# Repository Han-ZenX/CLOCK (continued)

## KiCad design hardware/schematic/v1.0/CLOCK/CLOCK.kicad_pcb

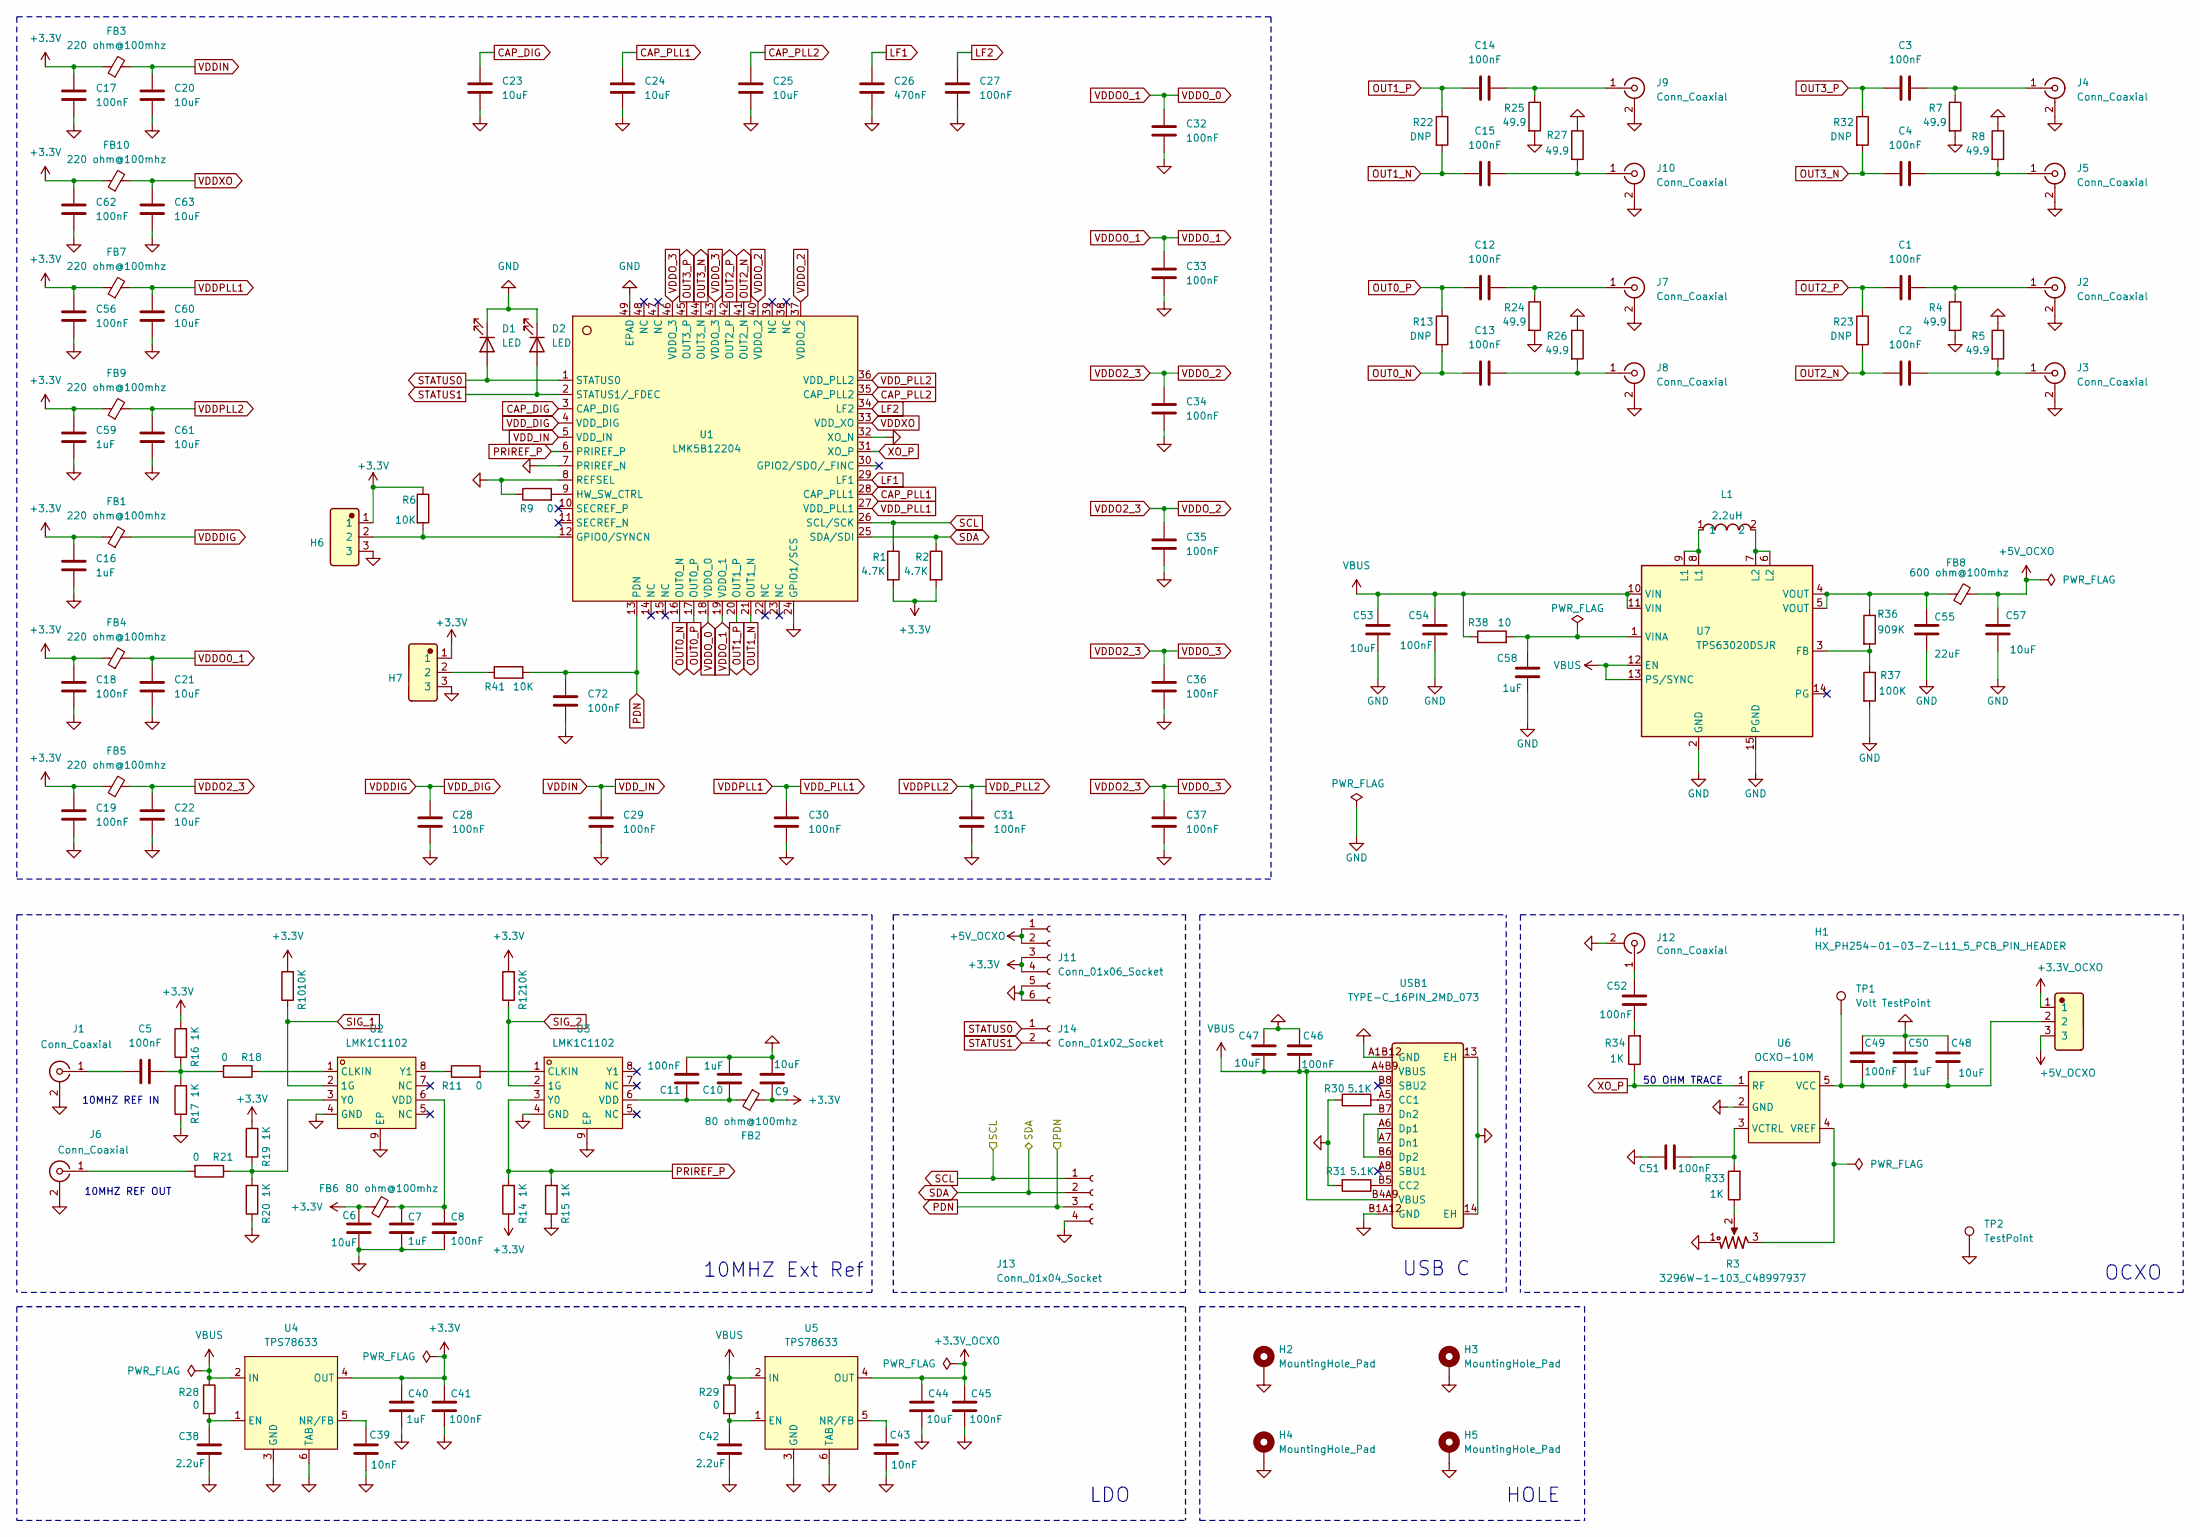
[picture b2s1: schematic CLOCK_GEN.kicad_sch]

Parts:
C1, C2, C3, C4, C5, C8, C11, C12, C13, C14, C15, C17, C18, C19, C27, C28, C29, C30, C31, C32, C33, C34, C35, C36, C37, C41, C45, C46, C49, C51, C52, C54, C56, C62, C72: 100nF; C_0402_1005Metric
C6, C9, C20, C21, C22, C23, C24, C25, C47, C60, C61, C63: 10uF; C_0402_1005Metric
C7, C10, C16, C40, C50, C59: 1uF; C_0402_1005Metric
C26: 470nF; C_0402_1005Metric
C38, C42: 2.2uF; C_0603_1608Metric
C39, C43: 10nF; C_0402_1005Metric
C44: 10uF; C_0805_2012Metric
C48, C53, C57: 10uF; C_0603_1608Metric
C55: 22uF; C_0805_2012Metric
C58: 1uF; C_0603_1608Metric
D1, D2: LED; LED_0603_1608Metric
FB1, FB3, FB4, FB5, FB7, FB9, FB10: 220 ohm@100mhz; L_0603_1608Metric
FB2, FB6: 80 ohm@100mhz; L_0603_1608Metric
FB8: 600 ohm@100mhz; L_0603_1608Metric
H1, H6, H7: HX_PH254-01-03-Z-L11_5_PCB_PIN_HEADER; Manufacturer Part HX PH254-01-03-Z-L11.5 pcb pin header; LCSC C52016391
H2, H3, H4, H5: MountingHole_Pad; MountingHole_3.2mm_M3_Pad
J1, J2, J3, J4, J5, J6, J7, J8, J9, J10, J12: Conn_Coaxial; SMA_Amphenol_132289_EdgeMount
J11: Conn_01x06_Socket; PinSocket_1x06_P2.54mm_Vertical
J13: Conn_01x04_Socket; PinHeader_1x04_P2.54mm_Vertical
J14: Conn_01x02_Socket; PinSocket_1x02_P2.54mm_Vertical
L1: 2.2uH; FNR4030S2R2MT; Manufacturer Part FNR4030S2R2MT; LCSC C167869
R1, R2: 4.7K; R_0603_1608Metric
R3: 3296W-1-103_C48997937; Manufacturer Part 3296W-1-103; LCSC C48997937
R4, R5, R7, R8, R24, R25, R26, R27: 49.9; R_0402_1005Metric
R6: 10K; R_0603_1608Metric
R9, R11, R18, R21, R28, R29: 0; R_0402_1005Metric
R10, R12, R41: 10K; R_0402_1005Metric
R13, R22, R23, R32: DNP; R_0402_1005Metric
R14, R15, R16, R17, R19, R20, R33, R34: 1K; R_0402_1005Metric
R30, R31: 5.1K; R_0402_1005Metric
R36: 909K; R_0603_1608Metric
R37: 100K; R_0603_1608Metric
R38: 10; R_0402_1005Metric
TP1: Volt TestPoint; TestPoint_Pad_D1.0mm
TP2: TestPoint; TestPoint_Loop_D1.80mm_Drill1.0mm_Beaded
U1: LMK5B12204; VQFN-48-1EP_7x7mm_P0.5mm_EP5.15x5.15mm_ThermalVias
U2, U3: LMK1C1102; WSON-8-1EP_2x2mm_P0.5mm_EP0.9x1.6mm
U4, U5: TPS78633; TPS78633DCQR
U6: OCXO-10M; DOPFITKR2-10M
U7: TPS63020DSJR
USB1: TYPE-C_16PIN_2MD_073; Manufacturer Part TYPE-C 16PIN 2MD(073); LCSC C2765186

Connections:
+3.3V: C6.2, C9.2, C16.2, C17.2, C18.2, C19.2, C40.1, C41.1, C56.2, C59.2, C62.2, FB1.1, FB2.1, FB3.1, FB4.1, FB5.1, FB6.1, FB7.1, FB9.1, FB10.1, H6.1, H7.1, J11.3, J11.4, R1.2, R2.2, R6.1, R10.2, R12.2, R14.1, R16.2, R19.2, U4.4 (OUT); also elsewhere on the board
+3.3V_OCXO: C44.1, C45.1, H1.1, U5.4 (OUT)
+5V_OCXO: C57.1, FB8.2, H1.3, J11.1, J11.2
CAP_DIG: C23.2, U1.3 (CAP_DIG)
CAP_PLL1: C24.2, U1.28 (CAP_PLL1)
CAP_PLL2: C25.2, U1.35 (CAP_PLL2)
GND: C6.1, C7.1, C8.1, C9.1, C10.1, C11.1, C16.1, C17.1, C18.1, C19.1, C20.1, C21.1, C22.1, C23.1, C24.1, C25.1, C26.1, C27.1, C28.1, C29.1, C30.1, C31.1, C32.1, C33.1, C34.1, C35.1, C36.1, C37.1, C38.1, C39.2, C40.2, C41.2, C42.1, C43.2, C44.2, C45.2, C46.2, C47.1, C48.1, C49.2, C50.1, C51.2, C53.2, C54.2, C55.2, C56.1, C57.2, C58.2, C59.1, C60.1, C61.1, C62.1, C63.1, C72.1, D1.1 (K), D2.1 (K), H2.1 (1_1), H3.1 (1_1), H4.1 (1_1), H5.1 (1_1), H6.3, H7.3, J1.2 (Ext), J2.2 (Ext), J3.2 (Ext), J4.2 (Ext), J5.2 (Ext), J6.2 (Ext), J7.2 (Ext), J8.2 (Ext), J9.2 (Ext), J10.2 (Ext), J11.5, J11.6, J12.2 (Ext), J13.4, R3.1, R4.2, R5.1, R7.2, R8.1, R9.1, R15.1, R17.1, R20.1, R24.2, R25.2, R26.1, R27.1, R30.1, R31.2, R37.2, TP2.1 (1_1), U1.7 (PRIREF_N), U1.8 (REFSEL), U1.24 (GPIO1/SCS), U1.32 (XO_N), U1.49 (EPAD), U2.4 (GND), U2.9 (EP), U3.4 (GND), U3.9 (EP), U4.3 (GND), U4.6 (TAB), U5.3 (GND), U5.6 (TAB), U6.2 (GND), U7.2 (GND), U7.15 (PGND), USB1.13 (EH), USB1.14 (EH), USB1.A1B12 (GND), USB1.B1A12 (GND); also elsewhere on the board
LF1: C26.2, U1.29 (LF1)
LF2: C27.2, U1.34 (LF2)
unnamed: C5.2, R16.1, R17.2, R18.2
unnamed: C52.2, R34.2
unnamed: C55.1, FB8.1, R36.1, U7.4 (VOUT), U7.5 (VOUT)
unnamed: H7.2, R41.1
unnamed: C5.1, J1.1 (In)
unnamed: C1.2, J2.1 (In), R4.1
unnamed: C2.2, J3.1 (In), R5.2
unnamed: C3.2, J4.1 (In), R7.1
unnamed: C4.1, J5.1 (In), R8.2
unnamed: J6.1 (In), R21.2
unnamed: C12.2, J7.1 (In), R24.1
unnamed: C13.2, J8.1 (In), R26.2
unnamed: C14.2, J9.1 (In), R25.1
unnamed: C15.1, J10.1 (In), R27.2
unnamed: C52.1, J12.1 (In)
unnamed: L1.1, U7.8 (L1), U7.9 (L1)
unnamed: L1.2, U7.6 (L2), U7.7 (L2)
unnamed: R3.2, R33.1
unnamed: H6.2, R6.2, U1.12 (GPIO0/SYNCN)
unnamed: R9.2, U1.9 (HW_SW_CTRL)
unnamed: R18.1, U2.1 (CLKIN)
unnamed: C7.2, C8.2, FB6.2, U2.6 (VDD)
unnamed: R19.1, R20.2, R21.1, U2.3 (Y0)
unnamed: R11.1, U2.8 (Y1)
unnamed: R11.2, U3.1 (CLKIN)
unnamed: C10.2, C11.2, FB2.2, U3.6 (VDD)
unnamed: C38.2, R28.2, U4.1 (EN)
unnamed: C39.1, U4.5 (NR/FB)
unnamed: C42.2, R29.2, U5.1 (EN)
unnamed: C43.1, U5.5 (NR/FB)
unnamed: C48.2, C49.1, C50.2, H1.2, TP1.1 (1_1), U6.5 (VCC)
unnamed: C51.1, R33.2, U6.3 (VCTRL)
unnamed: R3.3, U6.4 (VREF)
unnamed: R36.2, R37.1, U7.3 (FB)
unnamed: C58.1, R38.2, U7.1 (VINA)
unnamed: R30.2, USB1.A5 (CC1)
unnamed: R31.1, USB1.B5 (CC2)
unnamed: USB1.A6 (Dp1), USB1.A7 (Dn1)
unnamed: USB1.B6 (Dp2), USB1.B7 (Dn2)
OUT0_N: C13.1, R13.2, U1.16 (OUT0_N)
OUT0_P: C12.1, R13.1, U1.17 (OUT0_P)
OUT1_N: C15.2, R22.2, U1.21 (OUT1_N)
OUT1_P: C14.1, R22.1, U1.20 (OUT1_P)
OUT2_N: C2.1, R23.2, U1.41 (OUT2_N)
OUT2_P: C1.1, R23.1, U1.42 (OUT2_P)
OUT3_N: C4.2, R32.2, U1.44 (OUT3_N)
OUT3_P: C3.1, R32.1, U1.45 (OUT3_P)
PDN: C72.2, J13.3, R41.2, U1.13 (PDN); also elsewhere on the board
PRIREF_P: R14.2, R15.2, U1.6 (PRIREF_P), U3.3 (Y0)
SCL: J13.1, R1.1, U1.26 (SCL/SCK); also elsewhere on the board
SDA: J13.2, R2.1, U1.25 (SDA/SDI); also elsewhere on the board
SIG_1: R10.1, U2.2 (1G)
SIG_2: R12.1, U3.2 (1G)
STATUS0: D1.2 (A), J14.1, U1.1 (STATUS0)
STATUS1: D2.2 (A), J14.2, U1.2 (STATUS1/_FDEC)
VBUS: C46.1, C47.2, C53.1, C54.1, R28.1, R29.1, R38.1, U4.2 (IN), U5.2 (IN), U7.10 (VIN), U7.11 (VIN), U7.12 (EN), U7.13 (PS/SYNC), USB1.A4B9 (VBUS), USB1.B4A9 (VBUS)
VDDDIG: C28.2, FB1.2, U1.4 (VDD_DIG)
VDDIN: C20.2, C29.2, FB3.2, U1.5 (VDD_IN)
VDDO0_1: C21.2, C32.2, C33.2, FB4.2, U1.18 (VDDO_0), U1.19 (VDDO_1)
VDDO2_3: C22.2, C34.2, C35.2, C36.2, C37.2, FB5.2, U1.37 (VDDO_2), U1.40 (VDDO_2), U1.43 (VDDO_3), U1.46 (VDDO_3)
VDDPLL1: C30.2, C60.2, FB7.2, U1.27 (VDD_PLL1)
VDDPLL2: C31.2, C61.2, FB9.2, U1.36 (VDD_PLL2)
VDDXO: C63.2, FB10.2, U1.33 (VDD_XO)
XO_P: R34.1, U1.31 (XO_P), U6.1 (RF)

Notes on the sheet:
10MHZ REF IN
USB C
LDO
50 OHM TRACE
10MHZ Ext Ref
10MHZ REF OUT
HOLE
OCXO

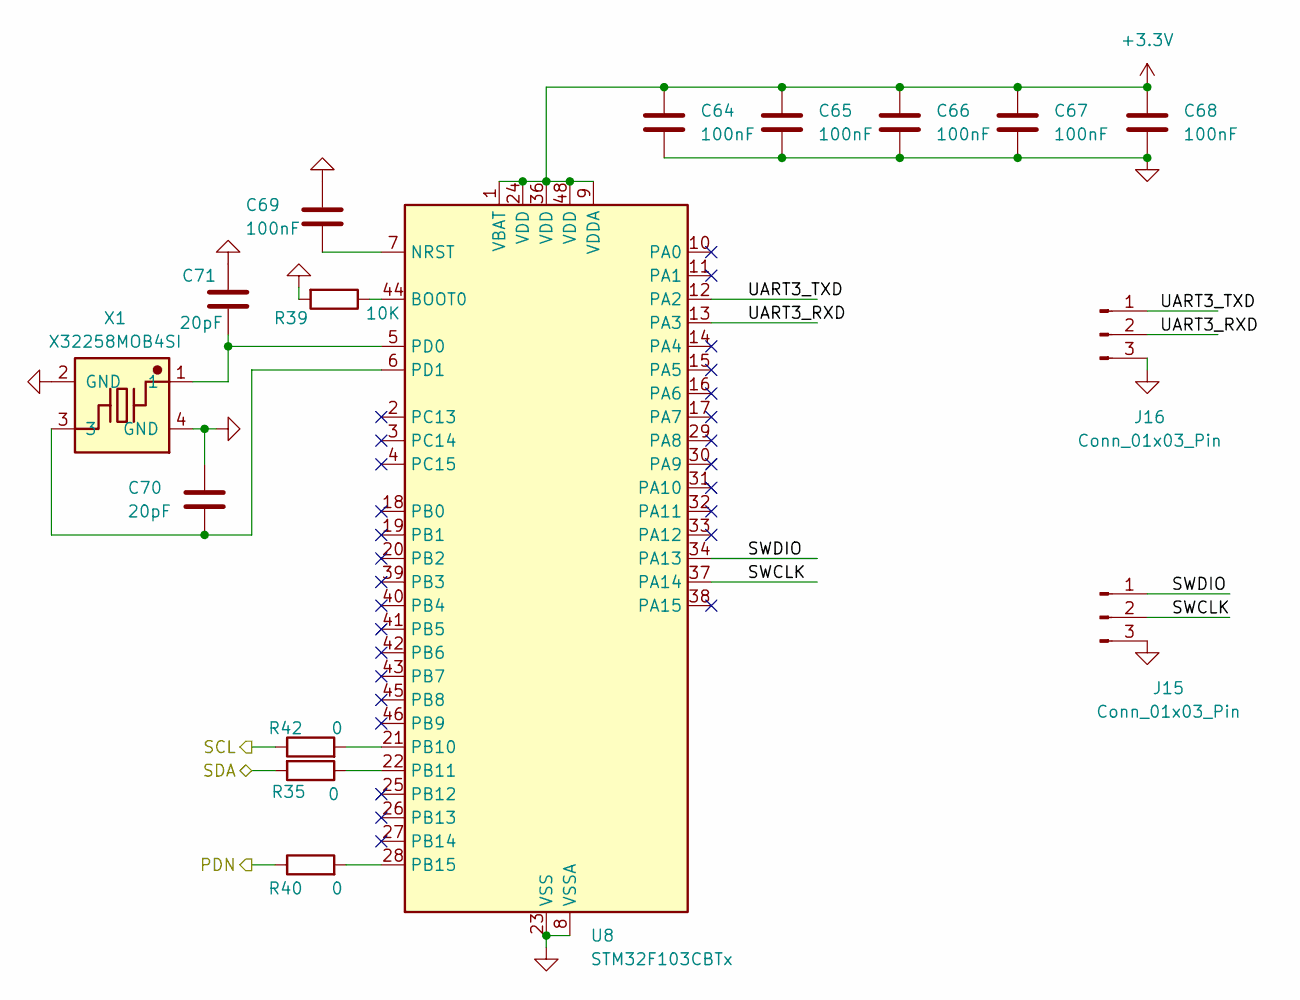
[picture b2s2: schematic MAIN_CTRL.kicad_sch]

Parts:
C64, C65, C66, C67, C68, C69: 100nF; C_0402_1005Metric
C70, C71: 20pF; C_0402_1005Metric
J15, J16: Conn_01x03_Pin; PinHeader_1x03_P2.54mm_Vertical
R35, R40, R42: 0; R_0402_1005Metric
R39: 10K; R_0603_1608Metric
U8: STM32F103CBTx; LQFP-48_7x7mm_P0.5mm
X1: X32258MOB4SI; Manufacturer Part X32258MOB4SI; LCSC C2682775

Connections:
+3.3V: C64.2, C65.2, C66.2, C67.2, C68.2, U8.1 (VBAT), U8.9 (VDDA), U8.24 (VDD), U8.36 (VDD), U8.48 (VDD); also elsewhere on the board
/MAIN_CTRL/SWCLK: J15.2, U8.37 (PA14)
/MAIN_CTRL/SWDIO: J15.1, U8.34 (PA13)
/MAIN_CTRL/UART3_RXD: J16.2, U8.13 (PA3)
/MAIN_CTRL/UART3_TXD: J16.1, U8.12 (PA2)
GND: C64.1, C65.1, C66.1, C67.1, C68.1, C69.2, C70.2, C71.2, J15.3, J16.3, R39.2, U8.8 (VSSA), U8.23 (VSS), U8.35 (VSS), U8.47 (VSS), X1.2 (GND), X1.4 (GND); also elsewhere on the board
unnamed: R39.1, U8.44 (BOOT0)
unnamed: C69.1, U8.7 (NRST)
unnamed: R42.2, U8.21 (PB10)
unnamed: R35.1, U8.22 (PB11)
unnamed: R40.2, U8.28 (PB15)
unnamed: C71.1, U8.5 (PD0), X1.1
unnamed: C70.1, U8.6 (PD1), X1.3
PDN: R40.1; also elsewhere on the board
SCL: R42.1; also elsewhere on the board
SDA: R35.2; also elsewhere on the board

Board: 4 copper layers, 162 parts (14 on the bottom side), 84 nets, no tracks yet.

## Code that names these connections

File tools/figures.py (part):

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    5: (-3.4375, -0.75, 'VDD_IN', 'pwr'), 6: (-3.4375, -0.25, 'PRIREF_P', 'clk'),
    7: (-3.4375, 0.25, 'PRIREF_N', 'gnd'), 8: (-3.4375, 0.75, 'REFSEL', 'gnd'),
    9: (-3.4375, 1.25, 'HW_SW_CTRL', 'log'), 10: (-3.4375, 1.75, 'SECREF_P', 'nc'),
    11: (-3.4375, 2.25, 'SECREF_N', 'nc'), 12: (-3.4375, 2.75, 'GPIO0', 'log'),
    13: (-2.75, 3.4375, 'PDN', 'log'), 14: (-2.25, 3.4375, 'NC', 'nc'),
    15: (-1.75, 3.4375, 'NC', 'nc'), 16: (-1.25, 3.4375, 'OUT0_N', 'out'),
    17: (-0.75, 3.4375, 'OUT0_P', 'out'), 18: (-0.25, 3.4375, 'VDDO_0', 'pwr'),
    19: (0.25, 3.4375, 'VDDO_1', 'pwr'), 20: (0.75, 3.4375, 'OUT1_P', 'out'),
    21: (1.25, 3.4375, 'OUT1_N', 'out'), 22: (1.75, 3.4375, 'NC', 'nc'),
    23: (2.25, 3.4375, 'NC', 'nc'), 24: (2.75, 3.4375, 'GPIO1', 'log'),
    25: (3.4375, 2.75, 'SDA', 'log'), 26: (3.4375, 2.25, 'SCL', 'log'),
    27: (3.4375, 1.75, 'VDD_PLL1', 'pwr'), 28: (3.4375, 1.25, 'CAP_PLL1', 'cap'),
    29: (3.4375, 0.75, 'LF1', 'cap'), 30: (3.4375, 0.25, 'GPIO2', 'log'),
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            _txt(d, x, yy, r, 5.8, FONT, DARK, anchor)

    side(CX - 4.5 * S, CY + 2.4 * S, '左侧 · DIG / IN 域', [
        'pin 3　CAP_DIG　10 µF',
        'pin 4　VDD_DIG　100 nF',
        'pin 5　VDD_IN　 100 nF',
        'pin 6　PRIREF_P　50 Ω 输入',
        'pin 7 / 8　直接接地',
    ], 'end')
    side(CX + 4.5 * S, CY + 2.9 * S, '右侧 · PLL1 / PLL2 / XO 域', [
        'pin 27　VDD_PLL1　100 nF',
        'pin 28　CAP_PLL1　10 µF',
        'pin 29　LF1　　　 470 nF',
        'pin 31　XO_P　　　50 Ω 输入',
        'pin 33　VDD_XO　　100 nF ← 缺件',
        'pin 34　LF2　　　 100 nF',
        'pin 35　CAP_PLL2　10 µF',
        'pin 36　VDD_PLL2　100 nF',
    ])
    _txt(d, CX, CY + 4.4 * S + 8, '顶边 · VDDO_2 / VDDO_3（pin 37 / 40 / 43 / 46）'
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    _txt(d, 14, 22, '左右两侧没有差分输出，11 颗电容全部走正面，内圈半径 4.9 mm；'
                    '顶底两边被 8 对差分输出占满，6 颗 100 nF 改到背面正对引脚。',
         6.2, BOLD, DARK)
    _txt(d, 14, 10, 'XO_P（pin 31）向右出线的 1.4 mm 通道必须留空——'
                    'VDD_XO 的 C64 与 LF1 的 C26 分列通道上下，不得越界。',
         6.2, FONT, DARK)
    return d
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         ('USB2ANY 适配器', 'TI 官方，可单独采购'),
         ('U1 LMK5B12204', '经 J13 接入板内 I2C'),
         'USB', 'SDA/SCL',
         '需让 U8 的 PB10/PB11 置高阻；J13 没有 GND 脚，地线要另接 TP2'),
        (12, '③ 由 U8 STM32 代劳（本项目推荐）', GREEN,
         colors.HexColor('#f7fbf3'),
         ('PC + TICS Pro', '只算频率、导出表'),
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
